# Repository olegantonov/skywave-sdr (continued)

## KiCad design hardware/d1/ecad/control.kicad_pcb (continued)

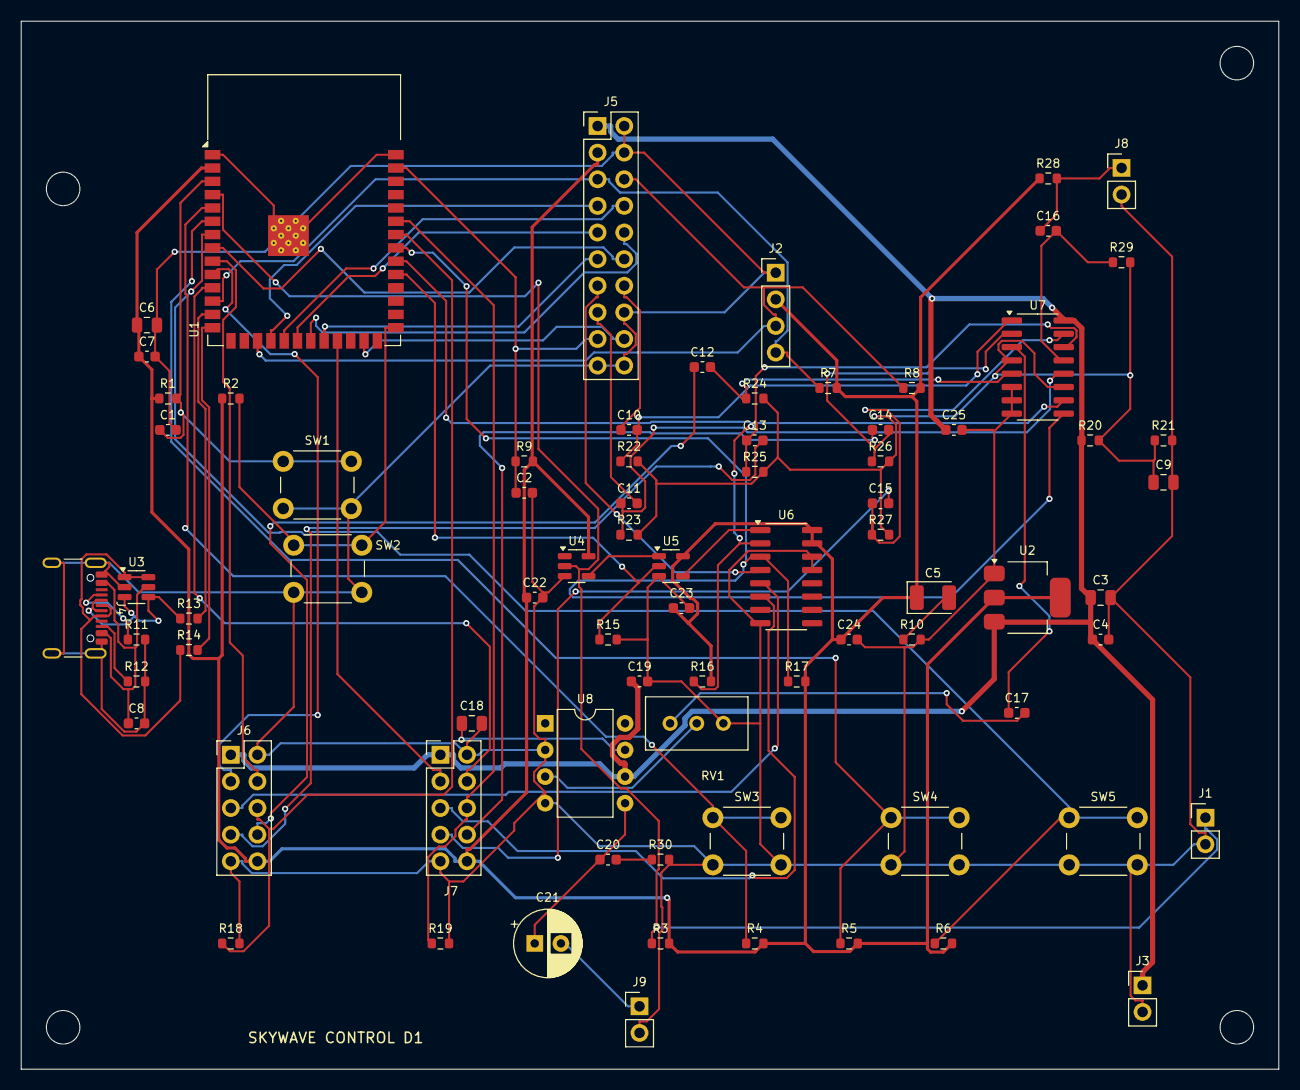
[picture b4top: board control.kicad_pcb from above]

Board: 2 copper layers, 120.0 x 100.0 mm, 82 parts (0 on the bottom side), 63 nets.

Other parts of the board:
H1, H2, H3, H4: MountingHole_3.2mm_M3

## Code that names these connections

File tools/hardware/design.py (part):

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    b=Board('control',120,100)
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    gpio_pads={4:4,5:5,6:6,7:7,15:8,16:9,17:10,18:11,8:12,19:13,20:14,3:15,46:16,9:17,10:18,11:19,12:20,13:21,14:22,21:23,47:24,48:25,45:26,0:27,35:28,36:29,37:30,38:31,39:32,40:33,41:34,42:35,44:36,43:37,2:38,1:39}
    p={1:pin('GND','GND','power_in'),2:pin('3V3','+3V3','power_in'),3:pin('EN','ESP_EN','input'),40:pin('GND','GND','power_in'),41:pin('EP','GND','power_in')}
    for g,n in gpio_pads.items(): p[n]=pin(f'IO{g}',gpio.get(g,'BOOT_N' if g==0 else None),'bidirectional')
    b.add('U','ESP32-S3-WROOM-1-N8','RF_Module:ESP32-S3-WROOM-1',p,(27,18),'esp32',3.25)
    b.r('10k','+3V3','ESP_EN',14,36); b.c('1u','ESP_EN','GND',14,39)
    b.r('10k','+3V3','BOOT_N',20,36)
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    b.add('C','22u tantalum','Capacitor_Tantalum_SMD:CP_EIA-3528-21_Kemet-B',{1:'+3V3',2:'LDO_ESR'},(87,55),'tantalum',2.1,mpn='T491B226K016AT')
    b.r('0.47','LDO_ESR','GND',85,59)
    b.c('10u','+3V3','GND',12,29); b.c('100n','+3V3','GND',12,32)
    usb={k:pin(k,'GND' if k in ['A1','A12','B1','B12','S1'] else 'VBUS_USB' if k in ['A4','A9','B4','B9'] else 'USB_DP_CONN' if k in ['A6','B6'] else 'USB_DM_CONN' if k in ['A7','B7'] else 'CC1' if k=='A5' else 'CC2' if k=='B5' else None)
         for k in ['A1','A4','A5','A6','A7','A8','A9','A12','B1','B4','B5','B6','B7','B8','B9','B12','S1']}
    b.add('J','USB4105-GF-A','Connector_USB:USB_C_Receptacle_GCT_USB4105-xx-A_16P_TopMnt_Horizontal',usb,(4,56),'usb',3.3,90)
    b.r('5.1k','CC1','GND',11,59); b.r('5.1k','CC2','GND',11,63)
    b.r('22','USB_DM_CONN','USB_DM',16,57); b.r('22','USB_DP_CONN','USB_DP',16,60)
    b.c('100n','VBUS_USB','GND',11,67)
    b.add('U','USBLC6-2SC6','Package_TO_SOT_SMD:SOT-23-6',{1:'USB_DP_CONN',2:'GND',3:'USB_DM_CONN',4:'USB_DM_CONN',5:'VBUS_USB',6:'USB_DP_CONN'},(11,54),'esd',1.1)
    b.add('U','SN74LVC1G04DBVR',SOT5,{1:None,2:pin('A','PTT_BUTTON_N','input'),3:'GND',4:pin('Y','PTT_PRESSED','output'),5:'+3V3'},(53,52),'inverter',1.45)
    b.add('U','SN74LVC1G00DBVR',SOT5,{1:pin('A','PTT_PRESSED','input'),2:pin('B','TX_ARM','input'),3:'GND',4:pin('Y','TX_ENABLE_N','output'),5:'+3V3'},(62,52),'nand',1.45)
    b.r('100k','TX_ARM','GND',56,59)
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    b.r('100k','MODULE_A','+3V3',65,63); b.r('100k','MODULE_B','+3V3',74,63)
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    b.r('2.2k','+3V3','MIC_RAW',98,15); b.c('1u','MIC_RAW','MIC_B',98,20); b.r('100k','MIC_B','VMID',105,23)
    b.c('1u','AUDIO_SELECTED','VOL_TOP',95,66)
    b.add('RV','10k volume','Potentiometer_THT:Potentiometer_Bourns_3296W_Vertical',{1:'GND',2:'AMP_IN',3:'VOL_TOP'},(105,69),'volume',10,mpn='3296W-1-103LF')
    b.add('U','LM386N-1','Package_DIP:DIP-8_W7.62mm',{1:None,2:'GND',3:pin('IN','AMP_IN','input'),4:'GND',5:pin('OUT','AMP_OUT','output'),6:'+5V',7:'AMP_BYPASS',8:None},(85,70),'audio_amp',5)
    b.c('10u','AMP_BYPASS','GND',78,73); b.c('100n','+5V','GND',92,72)
    b.c('100n','AMP_OUT','ZOBEL',84,83); b.r('10','ZOBEL','GND',89,83)
    b.add('C','220u','Capacitor_THT:CP_Radial_D6.3mm_P2.50mm',{1:'AMP_OUT',2:'SPEAKER'},(96,82),'electrolytic',11.2,mpn='EEUFR1A221')
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    for i,rail in enumerate(['+3V3','+1V8','+1V8','+3V3']): b.c('100n',rail,'GND',23+i*3,33)
    b.c('10u','CODEC_REF','GND',34,27); b.c('1u','AUDIO_RAW','HF_AUDIO',35,20); b.c('1u','HF_MIC','MIC_IN',35,23)
    b.r('10k','CODEC_RESET_N','GND',22,20)
    b.add('U','SI5351A-B-GT','Package_SO:MSOP-10_3x3mm_P0.5mm',{1:'+3V3',2:'XTAL_A',3:'XTAL_B',4:pin('SCL','I2C_SCL','input'),5:pin('SDA','I2C_SDA','bidirectional'),6:None,7:'+3V3',8:'GND',9:None,10:pin('CLK0','LO4_RAW','output')},(63,18),'si5351',1.1)
    b.add('Y','25MHz 10pF','Crystal:Crystal_SMD_3225-4Pin_3.2x2.5mm',{1:'XTAL_A',2:'GND',3:'XTAL_B',4:'GND'},(60,11),'crystal',.8,mpn='Abracon ABM8-25.000MHZ-10-1-U-T')
    b.c('100n','+3V3','GND',68,17); b.r('33','LO4_RAW','LO4',70,20)
    b.add('U','74LVC74APW','Package_SO:TSSOP-14_4.4x5mm_P0.65mm',{1:'LO_RESET_N',2:'LO_Q_N',3:'LO4',4:'+3V3',5:pin('1Q','LO_I','output'),6:None,7:'GND',8:pin('2Q_N','LO_Q_N','output'),9:pin('2Q','LO_Q','output'),10:'+3V3',11:'LO4',12:'LO_I',13:'LO_RESET_N',14:'+3V3'},(81,18),'flipflop',1.1)
    b.r('10k','LO_RESET_N','GND',85,12); b.c('100n','+3V3','GND',86,20)
    b.add('U','SN74LVC1G04DBVR',SOT5,{1:None,2:'HF_TX_N',3:'GND',4:pin('Y','HF_TX','output'),5:'+3V3'},(103,75),'inverter',1.45)
    b.r('10k','HF_TX_N','+3V3',109,74)
    b.r('10k','+5V','VMID_RAW',45,24); b.r('10k','VMID_RAW','GND',49,24); b.c('10u','VMID_RAW','GND',48,28)
    rxamp={1:pin('OUT1','RX_I','output'),2:'RX_I_NEG',3:'RX_I_POS',4:'+5V',5:'RX_Q_POS',6:'RX_Q_NEG',7:pin('OUT2','RX_Q','output'),8:pin('OUT3','VMID','output'),9:'VMID',10:'VMID_RAW',11:'GND',12:'VMID',13:'SPARE_OUT',14:pin('OUT4','SPARE_OUT','output')}
    b.add('U','TLV9064IDR',SO14,rxamp,(45,43),'opamp',1.75)
    for i,ch in enumerate(['I','Q']):
        y=35+i*18
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        b.r('1k','RX_'+ch,'LP_'+ch,36,y+6); b.c('10n','LP_'+ch,'GND',31,y+6)
        b.c('1u','LP_'+ch,'ADC_'+ch,27,y+6)
    b.c('100n','+5V','GND',40,40)
    txamp={1:pin('OUT1','TX_IP','output'),2:'TX_IP',3:'TX_I_BIAS',4:'+5V',5:'VMID',6:'TX_I_INV',7:pin('OUT2','TX_IN','output'),8:pin('OUT3','TX_QP','output'),9:'TX_QP',10:'TX_Q_BIAS',11:'GND',12:'VMID',13:'TX_Q_INV',14:pin('OUT4','TX_QN','output')}
    b.add('U','TLV9064IDR',SO14,txamp,(45,76),'opamp',1.75)
    for i,ch in enumerate(['I','Q']):
        y=65+i*22
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    b.header('CONTROL_INTERFACE',HT_HEADER,(5,51),2)
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    b.add('U','DRA818V' if name=='vhf' else 'DRA818U','SkyWave:DRA818',p,(30,37),name,6)
    b.add('U','TPS62160DGKR','Package_SO:VSSOP-8_3.0x3.0mm_P0.65mm',{1:'GND',2:'+5V',3:'+5V',4:'GND',5:'BUCK_FB',6:'+4V',7:pin('SW','BUCK_SW','output'),8:None},(40,59),'buck',1.1)
    b.add('L','2.2u','SkyWave:VLS3015ET',{1:'BUCK_SW',2:'+4V'},(46,59),'power_inductor',1.5,mpn='VLS3015ET-2R2M')
    b.c('10u','+5V','GND',35,59); b.c('22u','+4V','GND',47,64)
    b.r('402k','+4V','BUCK_FB',39,65); b.r('100k','BUCK_FB','GND',35,65)
    b.c('100n','+4V','GND',13,43); b.c('22u','+4V','GND',13,47)
    b.r('1k','UART_IN','UART_IN_R',49,43)
    b.add('U','SN74LVC1G17DBVR',SOT5,{1:None,2:'UART_OUT_RAW',3:'GND',4:pin('Y','UART_OUT','output'),5:'+3V3'},(50,51),'uart_buffer',1.45)
    b.add('U','SN74LVC1G04DBVR',SOT5,{1:None,2:'PTT_N',3:'GND',4:pin('Y','PTT_GATE','output'),5:'+3V3'},(22,57),'inverter',1.45)
    b.add('Q','2N7002','Package_TO_SOT_SMD:SOT-23',{1:'PTT_GATE',2:'GND',3:'DRA_PTT_N'},(26,51),'mosfet',1.1)
    b.r('10k','DRA_PTT_N','+4V',23,47); b.r('100k','PTT_GATE','GND',30,53)
    b.r('100k','PD','GND',17,53); b.r('10k','PTT_N','+3V3',19,62)
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
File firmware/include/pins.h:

#pragma once

namespace pins {
// Proposed wiring for a separate SkyWave prototype, not the SkySentinel wiring.
constexpr int OLED_SDA = 8;
constexpr int OLED_SCL = 9;
constexpr int PTT = 4;
constexpr int TUNE_DOWN = 5;
constexpr int TUNE_UP = 6;
constexpr int BAND = 7;
constexpr int USB_DM = 19;
constexpr int USB_DP = 20;
constexpr int TX_ARM = 38;
constexpr int MODULE_A = 39;
constexpr int MODULE_B = 40;
constexpr int VHF_PD = 41;
constexpr int UHF_PD = 42;
constexpr int CODEC_RESET_N = 15;
constexpr int LO_RESET_N = 48;
}
